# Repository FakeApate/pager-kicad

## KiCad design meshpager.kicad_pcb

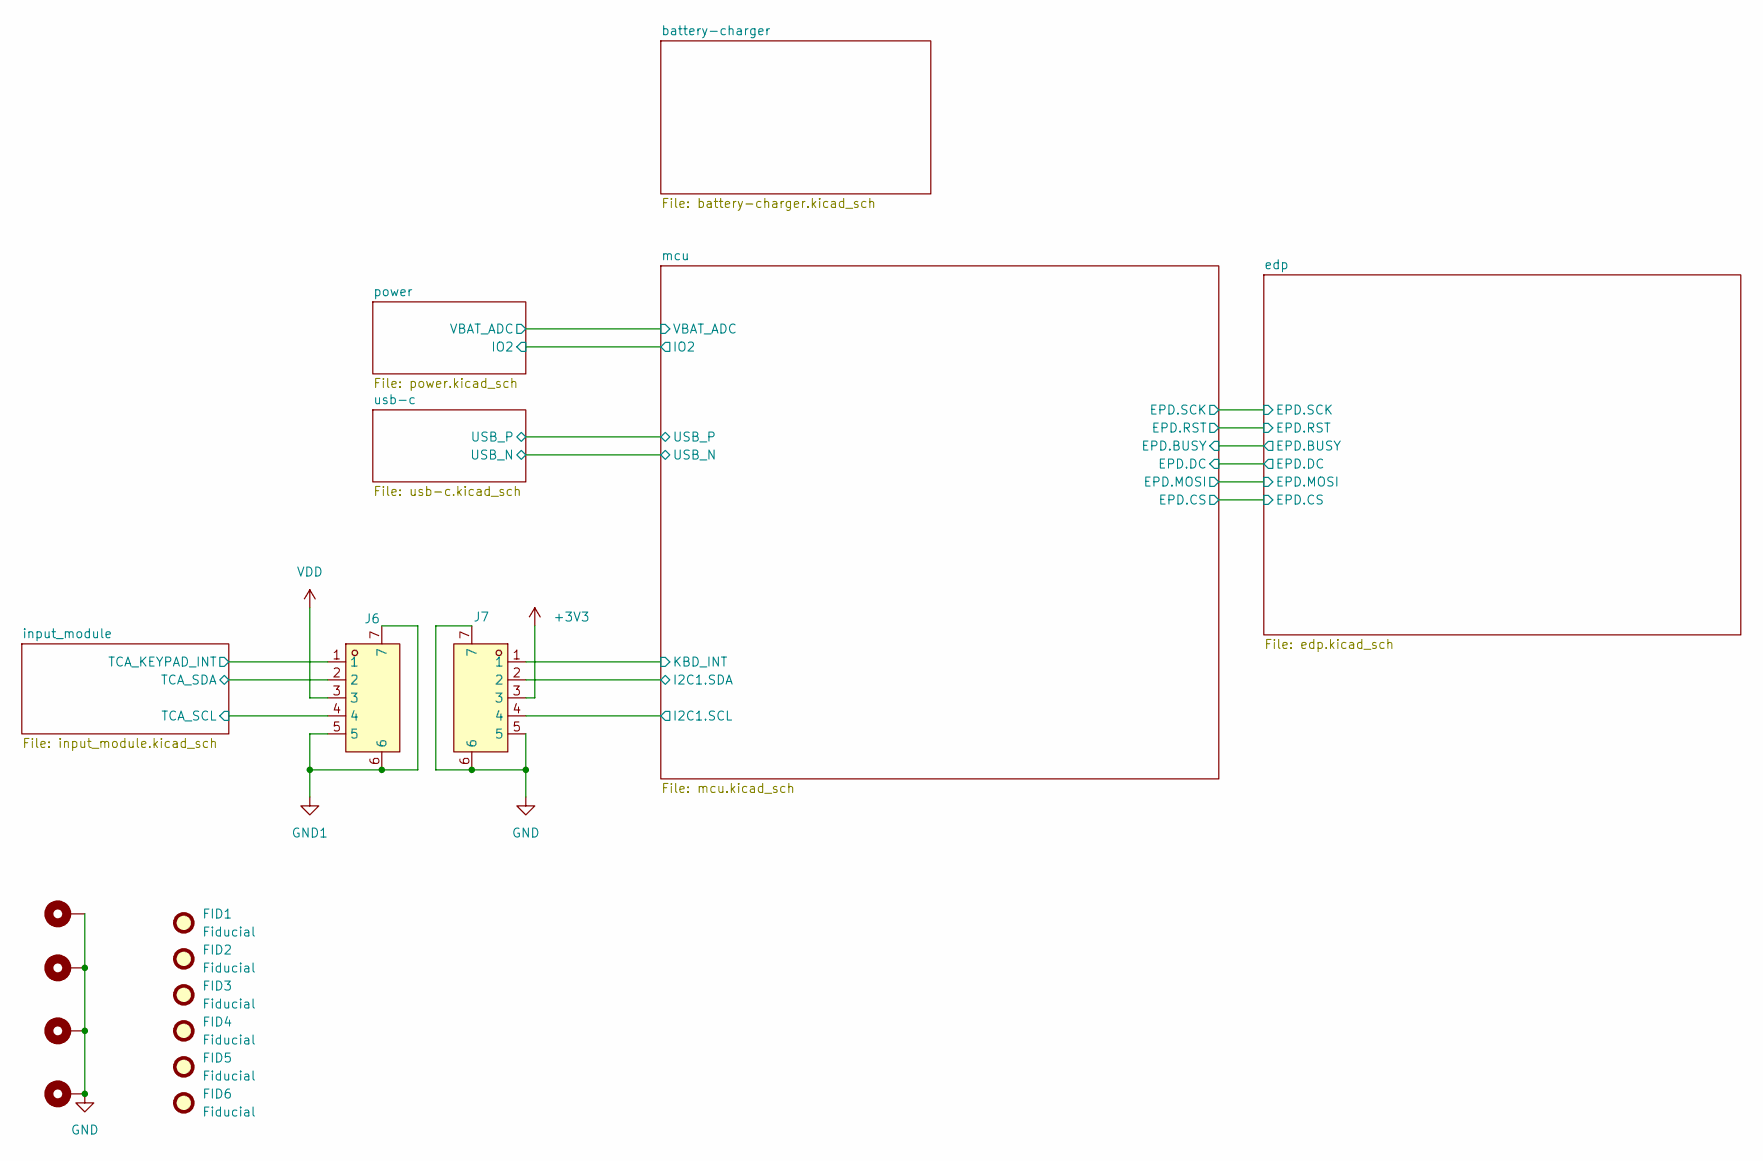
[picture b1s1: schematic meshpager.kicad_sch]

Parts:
FID1, FID2, FID3, FID4, FID5, FID6: Fiducial; Fiducial_1mm_Mask3mm
H5, H6, H7, H8: MountingHole_Pad; MountingHole_2.7mm_M2.5_Pad
J6, J7: HC-FPC-05-09-5RLTAG; CONN-SMD_5P-P0.50_HCTL_HC-FPC-05-09-5RLTAG; MPN HC-FPC-05-09-5RLTAG; LCSC Part C5213747

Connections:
+3V3: J7.3; also elsewhere on the board
/input_module/INT: J6.1; also elsewhere on the board
/input_module/TCA_SCL: J6.4; also elsewhere on the board
/input_module/TCA_SDA: J6.2; also elsewhere on the board
/mcu/I2C1.SCL: J7.4; also elsewhere on the board
/mcu/I2C1.SDA: J7.2; also elsewhere on the board
/mcu/KBD_INT: J7.1; also elsewhere on the board
GND: H5.1 (1_1), H6.1 (1_1), H7.1 (1_1), H8.1 (1_1), J7.5, J7.6, J7.7; also elsewhere on the board
GND1: J6.5, J6.6, J6.7; also elsewhere on the board
VDD: J6.3; also elsewhere on the board

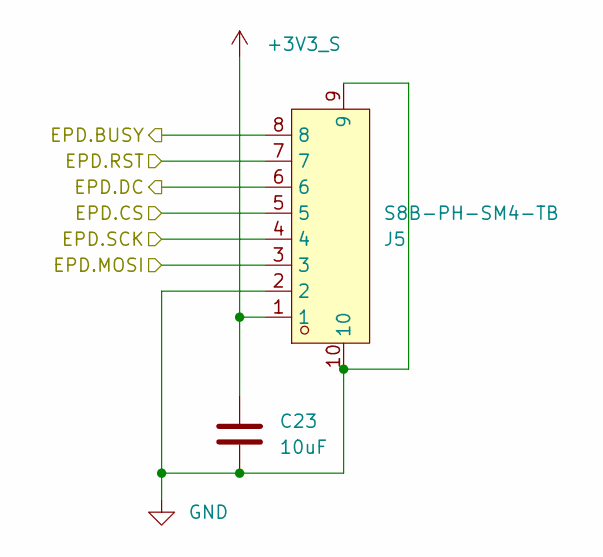
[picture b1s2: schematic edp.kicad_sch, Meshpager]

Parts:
C23: 10uF; C_0603_1608Metric; LCSC C19702
J5: S8B-PH-SM4-TB; CONN-SMD_8P-P2.00_S8B-PH-SM4-TB-LF-SN; MPN S8B-PH-SM4-TB(LF)(SN); LCSC Part C265121

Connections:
+3V3_S: C23.1, J5.1; also elsewhere on the board
/edp/EPD.BUSY: J5.8; also elsewhere on the board
/edp/EPD.CS: J5.5; also elsewhere on the board
/edp/EPD.DC: J5.6; also elsewhere on the board
/edp/EPD.MOSI: J5.3; also elsewhere on the board
/edp/EPD.RST: J5.7; also elsewhere on the board
/edp/EPD.SCK: J5.4; also elsewhere on the board
GND: C23.2, J5.2, J5.9, J5.10; also elsewhere on the board

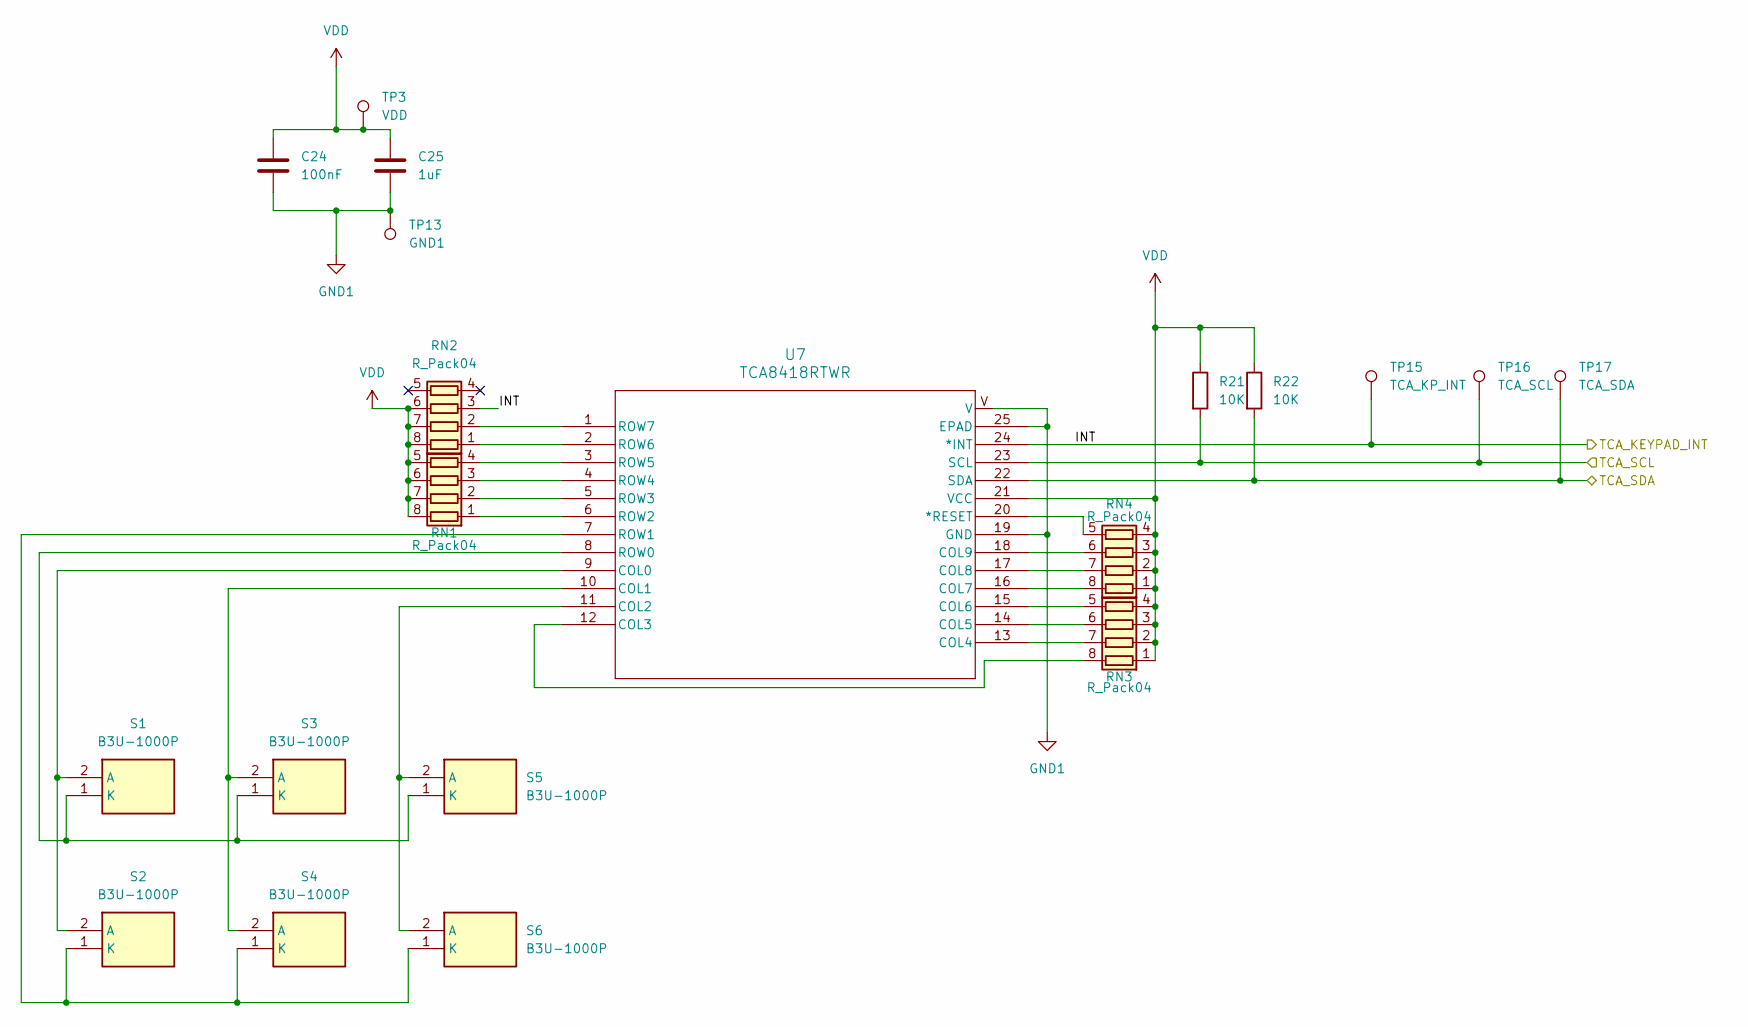
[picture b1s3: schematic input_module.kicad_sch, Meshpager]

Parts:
C24: 100nF; C_0402_1005Metric; LCSC C1525
C25: 1uF; C_0603_1608Metric; LCSC C15849
R21, R22: 10K; R_0402_1005Metric; LCSC C25744
RN1, RN2, RN3, RN4: R_Pack04; R_Array_Convex_4x0603; LCSC C29718
S1, S2, S3, S4, S5, S6: B3U-1000P; Mouser Part Number 653-B3U-1000P
TP3: VDD; TestPoint_Pad_D1.5mm
TP13: GND1; TestPoint_Pad_D1.5mm
TP15: TCA_KP_INT; TestPoint_Pad_D1.5mm
TP16: TCA_SCL; TestPoint_Pad_D1.5mm
TP17: TCA_SDA; TestPoint_Pad_D1.5mm
U7: TCA8418RTWR; WQFN-24-1EP_4x4mm_P0.5mm_EP2.45x2.45mm; LCSC C138713

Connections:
/input_module/INT: RN2.3 (R3.1), TP15.1 (1_1), U7.24 (*INT); also elsewhere on the board
/input_module/TCA_SCL: R21.2, TP16.1 (1_1), U7.23 (SCL); also elsewhere on the board
/input_module/TCA_SDA: R22.2, TP17.1 (1_1), U7.22 (SDA); also elsewhere on the board
GND1: C24.2, C25.2, TP13.1 (1_1), U7.19 (GND), U7.25 (EPAD), U7.V; also elsewhere on the board
unnamed: RN1.1 (R1.1), U7.6 (ROW2)
unnamed: RN1.2 (R2.1), U7.5 (ROW3)
unnamed: RN1.3 (R3.1), U7.4 (ROW4)
unnamed: RN1.4 (R4.1), U7.3 (ROW5)
unnamed: RN2.1 (R1.1), U7.2 (ROW6)
unnamed: RN2.2 (R2.1), U7.1 (ROW7)
unnamed: RN3.8 (R1.2), U7.12 (COL3)
unnamed: RN3.7 (R2.2), U7.13 (COL4)
unnamed: RN3.6 (R3.2), U7.14 (COL5)
unnamed: RN3.5 (R4.2), U7.15 (COL6)
unnamed: RN4.8 (R1.2), U7.16 (COL7)
unnamed: RN4.7 (R2.2), U7.17 (COL8)
unnamed: RN4.6 (R3.2), U7.18 (COL9)
unnamed: RN4.5 (R4.2), U7.20 (*RESET)
unnamed: S1.2 (A), S2.2 (A), U7.9 (COL0)
unnamed: S1.1 (K), S3.1 (K), S5.1 (K), U7.8 (ROW0)
unnamed: S2.1 (K), S4.1 (K), S6.1 (K), U7.7 (ROW1)
unnamed: S3.2 (A), S4.2 (A), U7.10 (COL1)
unnamed: S5.2 (A), S6.2 (A), U7.11 (COL2)
VDD: C24.1, C25.1, R21.1, R22.1, RN1.5 (R4.2), RN1.6 (R3.2), RN1.7 (R2.2), RN1.8 (R1.2), RN2.6 (R3.2), RN2.7 (R2.2), RN2.8 (R1.2), RN3.1 (R1.1), RN3.2 (R2.1), RN3.3 (R3.1), RN3.4 (R4.1), RN4.1 (R1.1), RN4.2 (R2.1), RN4.3 (R3.1), RN4.4 (R4.1), TP3.1 (1_1), U7.21 (VCC); also elsewhere on the board

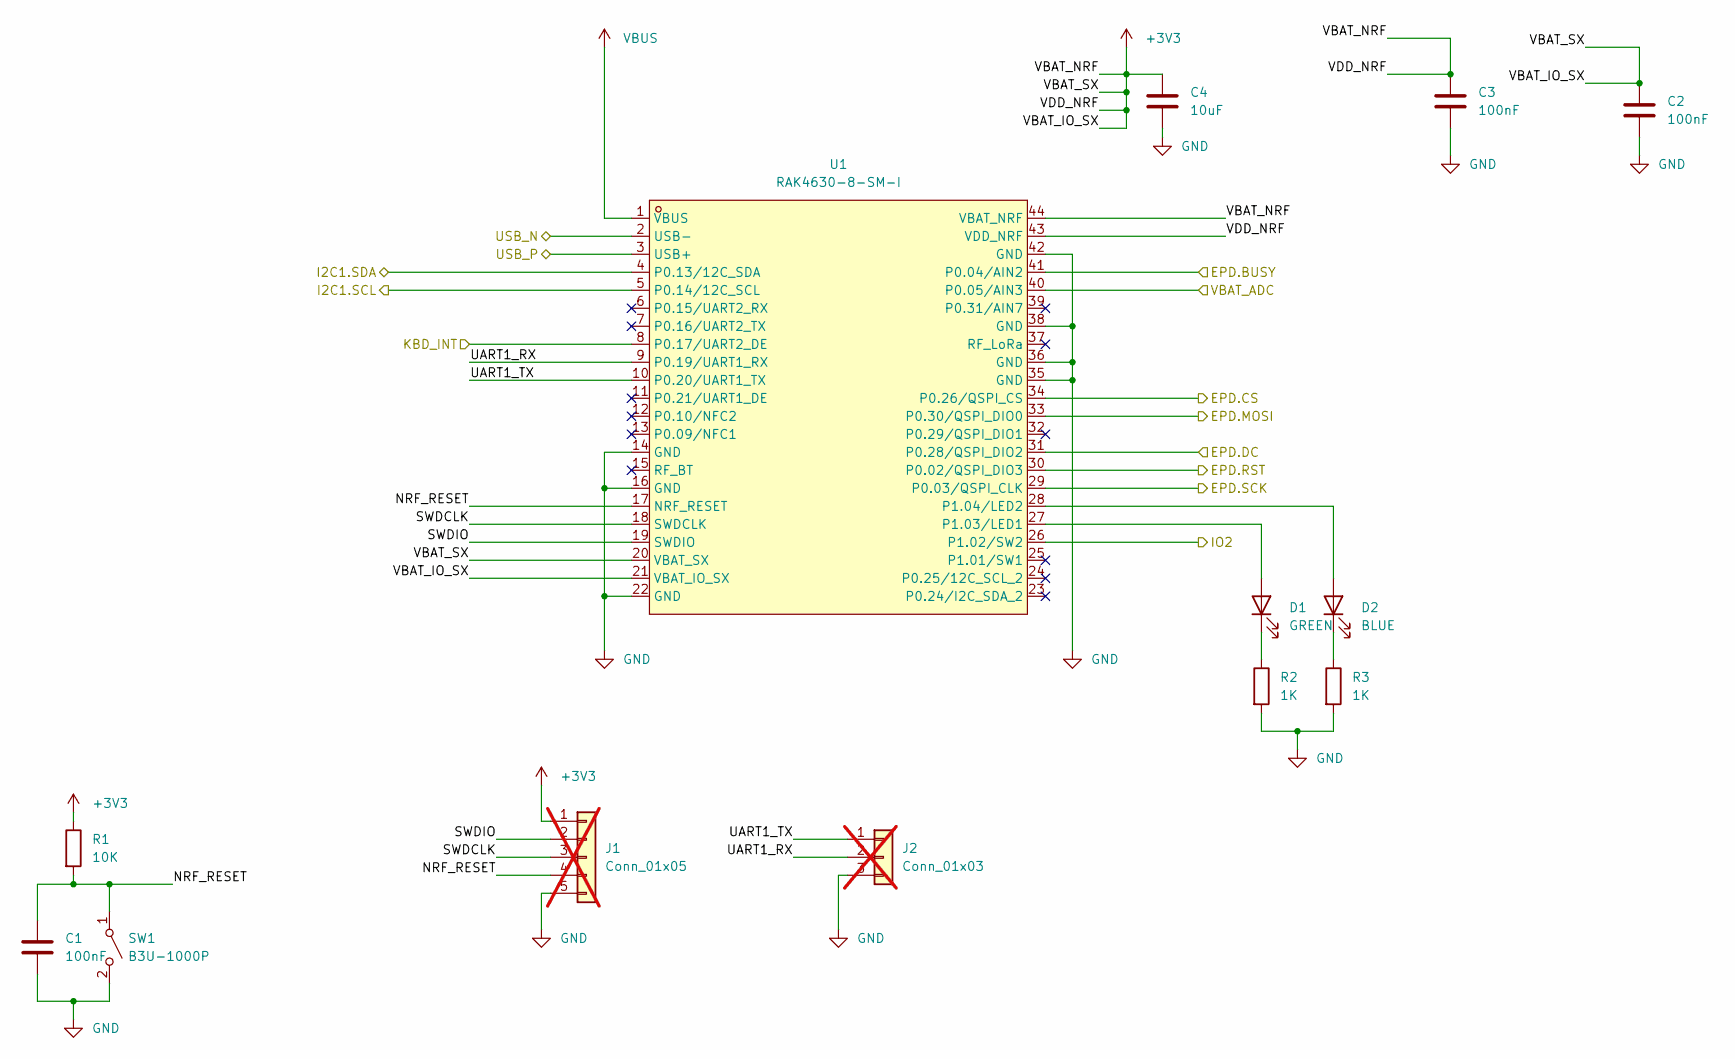
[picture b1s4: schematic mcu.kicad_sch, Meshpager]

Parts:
C1, C2, C3: 100nF; C_0402_1005Metric; LCSC C1525
C4: 10uF; C_0603_1608Metric; LCSC C19702
D1: GREEN; LED_0603_1608Metric; LCSC C12624
D2: BLUE; LED_0603_1608Metric; LCSC C2288
J1: Conn_01x05; PinHeader_1x05_P1.27mm_Vertical; not fitted
J2: Conn_01x03; PinHeader_1x03_P1.27mm_Vertical; not fitted
R1: 10K; R_0402_1005Metric; LCSC C25744
R2, R3: 1K; R_0402_1005Metric; LCSC C11702
SW1: B3U-1000P; LCSC C231329
U1: RAK4630-8-SM-I; COMM-SMD_44P-L23.0-W15.0-P1.20_RAK4630-8-SM-I; MPN RAk4630-8-SM-I; LCSC Part C32315253

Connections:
+3V3: C2.1, C3.1, C4.1, J1.1, R1.1, U1.20 (VBAT_SX), U1.21 (VBAT_IO_SX), U1.43 (VDD_NRF), U1.44 (VBAT_NRF); also elsewhere on the board
/edp/EPD.BUSY: U1.41 (P0.04/AIN2); also elsewhere on the board
/edp/EPD.CS: U1.34 (P0.26/QSPI_CS); also elsewhere on the board
/edp/EPD.DC: U1.31 (P0.28/QSPI_DIO2); also elsewhere on the board
/edp/EPD.MOSI: U1.33 (P0.30/QSPI_DIO0); also elsewhere on the board
/edp/EPD.RST: U1.30 (P0.02/QSPI_DIO3); also elsewhere on the board
/edp/EPD.SCK: U1.29 (P0.03/QSPI_CLK); also elsewhere on the board
/mcu/I2C1.SCL: U1.5 (P0.14/12C_SCL); also elsewhere on the board
/mcu/I2C1.SDA: U1.4 (P0.13/12C_SDA); also elsewhere on the board
/mcu/IO2: U1.26 (P1.02/SW2); also elsewhere on the board
/mcu/KBD_INT: U1.8 (P0.17/UART2_DE); also elsewhere on the board
/mcu/NRF_RESET: C1.1, J1.4, R1.2, SW1.1 (A), U1.17 (NRF_RESET)
/mcu/SWDCLK: J1.3, U1.18 (SWDCLK)
/mcu/SWDIO: J1.2, U1.19 (SWDIO)
/mcu/UART1_RX: J2.2, U1.9 (P0.19/UART1_RX)
/mcu/UART1_TX: J2.1, U1.10 (P0.20/UART1_TX)
/mcu/USB_N: U1.2 (USB-); also elsewhere on the board
/mcu/USB_P: U1.3 (USB+); also elsewhere on the board
/mcu/VBAT_ADC: U1.40 (P0.05/AIN3); also elsewhere on the board
GND: C1.2, C2.2, C3.2, C4.2, J1.5, J2.3, R2.2, R3.2, SW1.2 (B), U1.14 (GND), U1.16 (GND), U1.22 (GND), U1.35 (GND), U1.36 (GND), U1.38 (GND), U1.42 (GND); also elsewhere on the board
unnamed: D1.2 (A), U1.27 (P1.03/LED1)
unnamed: D1.1 (K), R2.1
unnamed: D2.2 (A), U1.28 (P1.04/LED2)
unnamed: D2.1 (K), R3.1
VBUS: U1.1 (VBUS); also elsewhere on the board

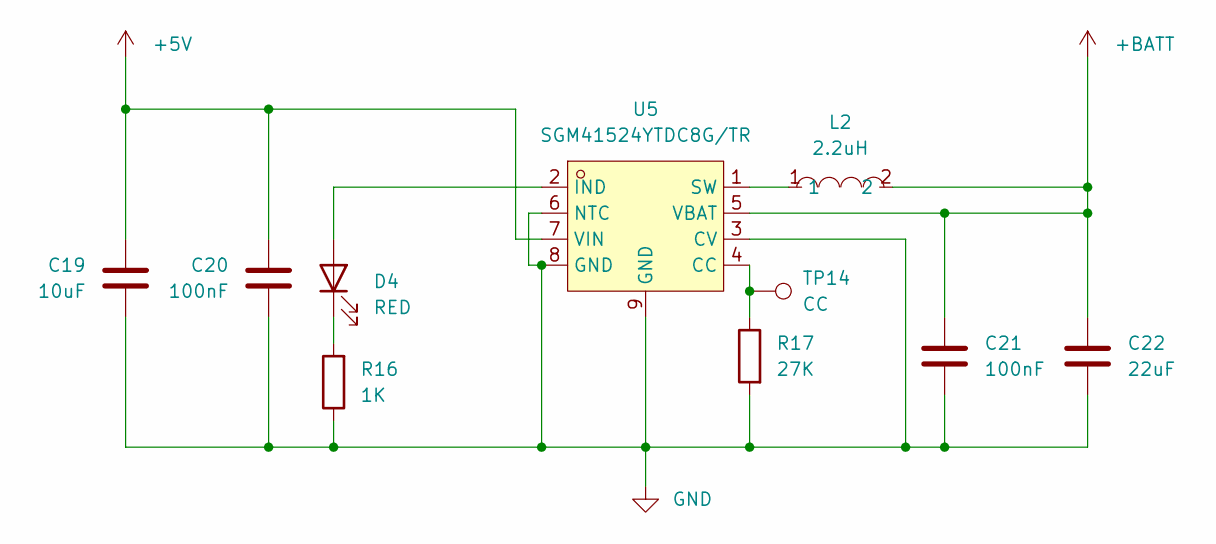
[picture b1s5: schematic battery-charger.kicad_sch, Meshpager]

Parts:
C19: 10uF; C_0603_1608Metric; LCSC C19702
C20, C21: 100nF; C_0402_1005Metric; LCSC C1525
C22: 22uF; C_0805_2012Metric; LCSC C45783
D4: RED; LED_0603_1608Metric; LCSC C2286
L2: 2.2uH; IND-SMD_L3.0-W3.0_SWPA3010S; MPN SWPA3012S2R2MT; LCSC Part C36402
R16: 1K; R_0402_1005Metric; LCSC C11702
R17: 27K; R_0402_1005Metric; LCSC C2933084
TP14: CC; TestPoint_Pad_D1.5mm
U5: SGM41524YTDC8G/TR; DFN-8_L3.0-W2.0-P0.50-TL-EP-1; MPN SGM41524YTDC8G/TR; LCSC Part C699852

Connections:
+5V: C19.2, C20.1, U5.7 (VIN); also elsewhere on the board
+BATT: C21.1, C22.2, L2.2, U5.5 (VBAT); also elsewhere on the board
GND: C19.1, C20.2, C21.2, C22.1, R16.1, R17.2, U5.3 (CV), U5.6 (NTC), U5.8 (GND), U5.9 (GND); also elsewhere on the board
unnamed: D4.2 (A), U5.2 (IND)
unnamed: D4.1 (K), R16.2
unnamed: R17.1, TP14.1 (1_1), U5.4 (CC)
unnamed: L2.1, U5.1 (SW)

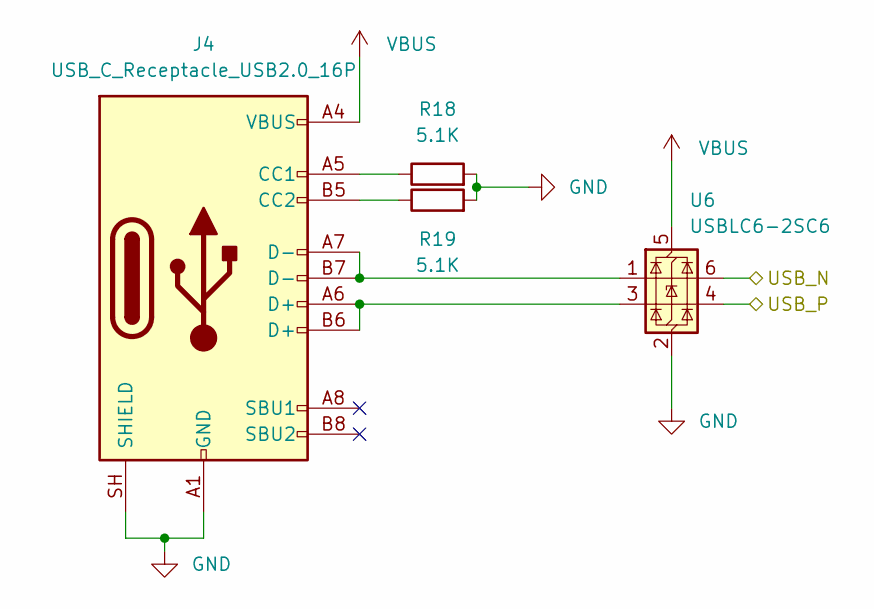
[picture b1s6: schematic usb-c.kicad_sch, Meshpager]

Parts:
J4: USB_C_Receptacle_USB2.0_16P; USB_C_Receptacle_G-Switch_GT-USB-7010ASV; LCSC Part C2988369
R18, R19: 5.1K; R_0402_1005Metric; LCSC C25905
U6: USBLC6-2SC6; SOT-23-6; LCSC C7519

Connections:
/mcu/USB_N: U6.6 (I/O1); also elsewhere on the board
/mcu/USB_P: U6.4 (I/O2); also elsewhere on the board
GND: J4.A1 (GND), J4.A12 (GND), J4.B1 (GND), J4.B12 (GND), J4.SH (SHIELD), R18.2, R19.2, U6.2 (GND); also elsewhere on the board
unnamed: J4.A5 (CC1), R18.1
unnamed: J4.B5 (CC2), R19.1
unnamed: J4.A6 (D+), J4.B6 (D+), U6.3 (I/O2)
unnamed: J4.A7 (D-), J4.B7 (D-), U6.1 (I/O1)
VBUS: J4.A4 (VBUS), J4.A9 (VBUS), J4.B4 (VBUS), J4.B9 (VBUS), U6.5 (VBUS); also elsewhere on the board

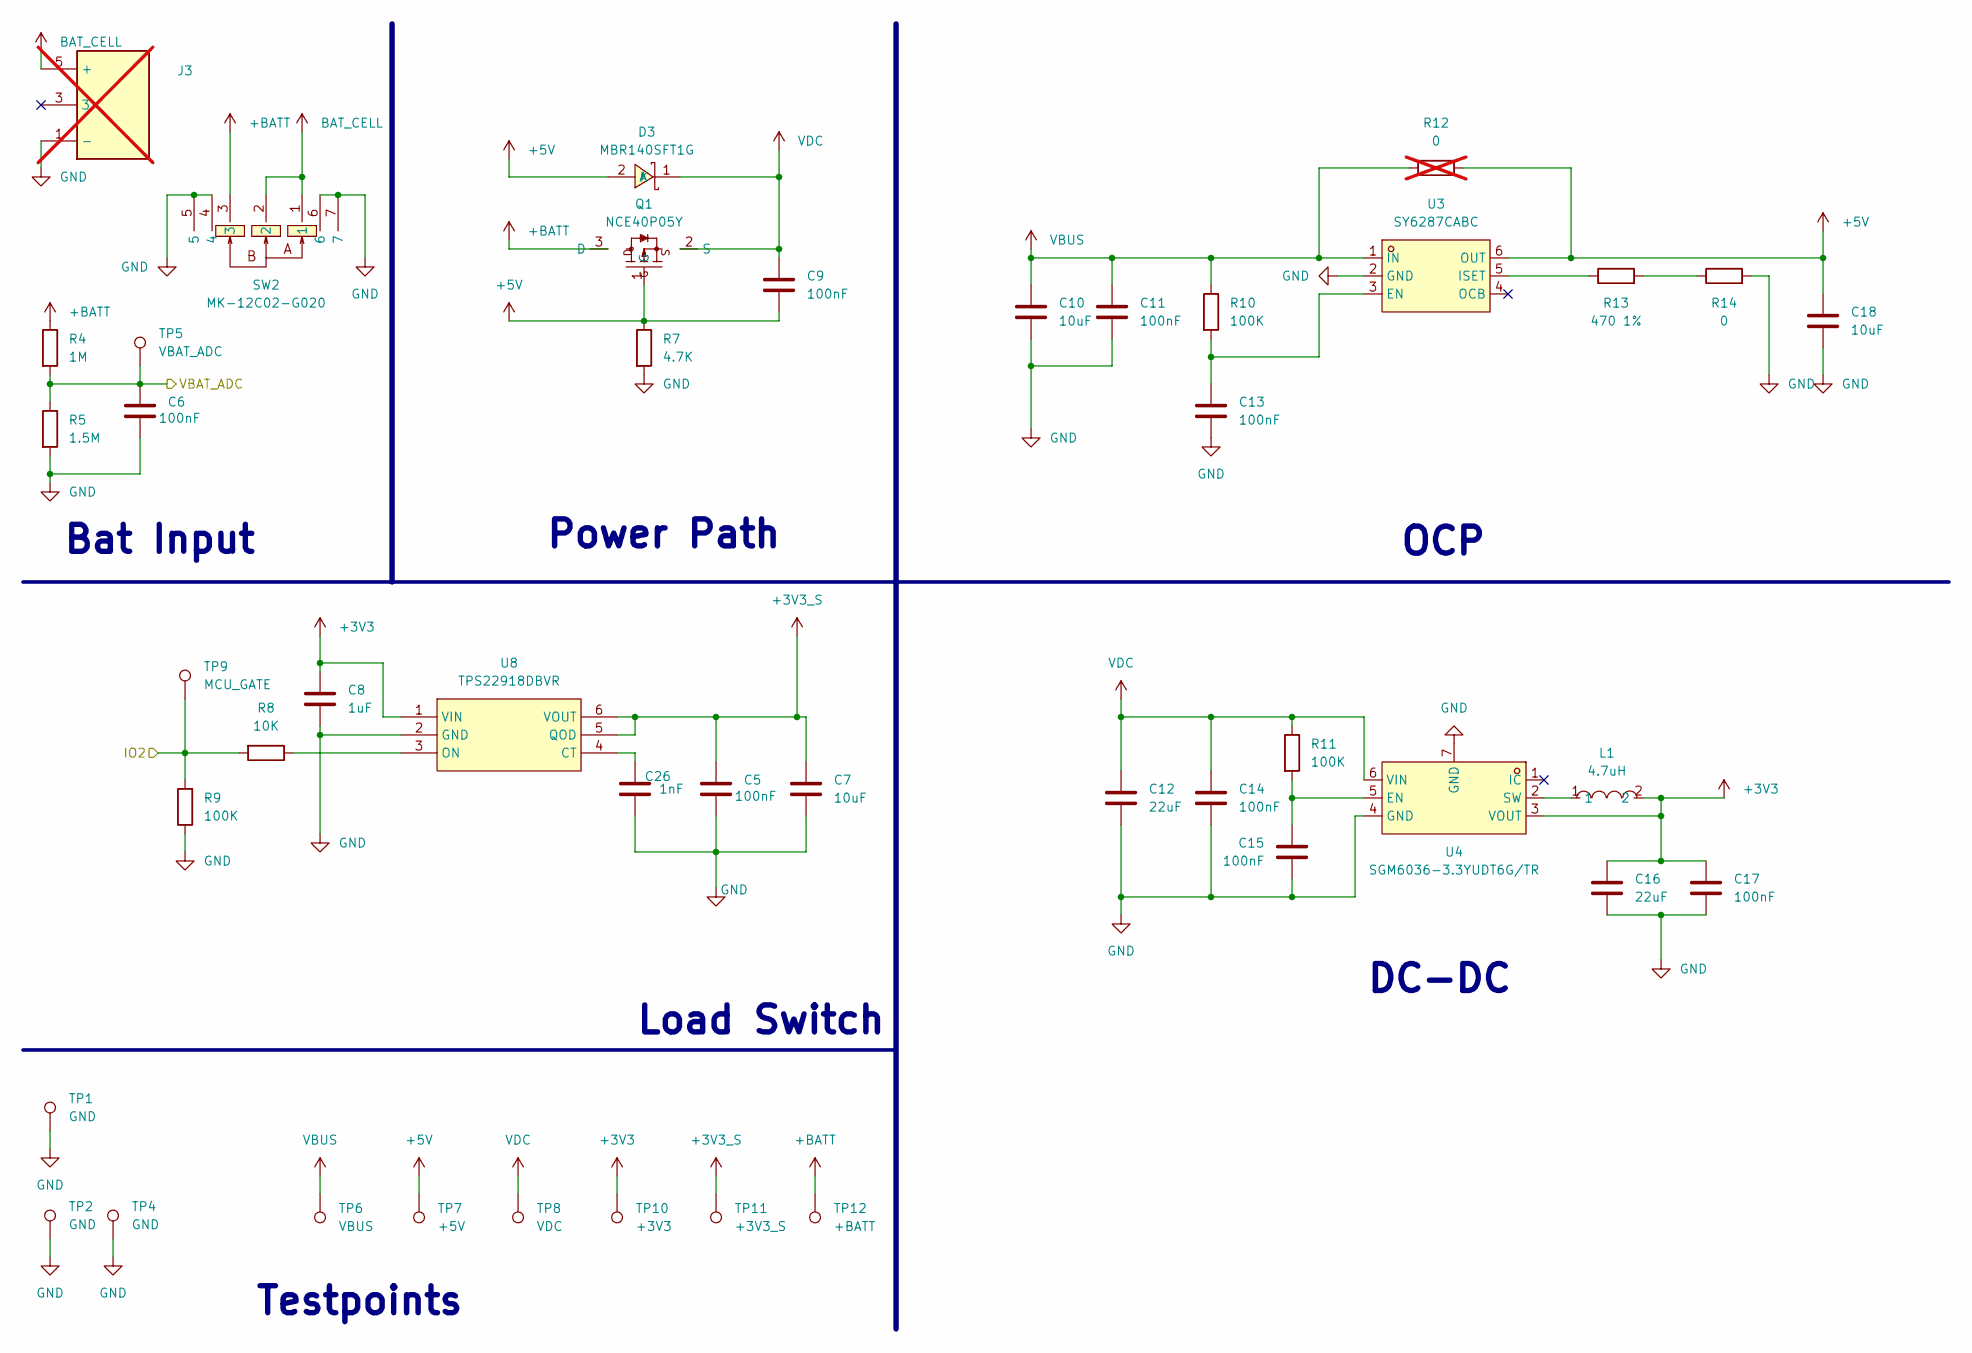
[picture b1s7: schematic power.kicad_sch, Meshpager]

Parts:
C5, C6, C9, C11, C13, C14, C15, C17: 100nF; C_0402_1005Metric; LCSC C1525
C7, C10, C18: 10uF; C_0603_1608Metric; LCSC C19702
C8: 1uF; C_0603_1608Metric; LCSC C15849
C12, C16: 22uF; C_0805_2012Metric; LCSC C45783
C26: 1nF; C_0402_1005Metric
D3: MBR140SFT1G; SOD-123F_L2.8-W1.8-LS3.7-RD; MPN MBR140SFT1G; LCSC Part C43381
J3: 009155003301006; Mouser Part Number 581-009155003301006; not fitted
L1: 4.7uH; IND-SMD_L3.0-W3.0_FNR30XXS; MPN SWPA3012S4R7MT; LCSC Part C83415
Q1: NCE40P05Y; SOT-23-3_L2.9-W1.6-P1.90-LS2.8-BR; MPN NCE40P05Y; LCSC Part C163738
R4: 1M; R_0402_1005Metric; LCSC C26083
R5: 1.5M; R_0402_1005Metric; LCSC C22276
R7: 4.7K; R_0402_1005Metric; LCSC C25900
R8: 10K; R_0402_1005Metric; LCSC C25744
R9, R10, R11: 100K; R_0402_1005Metric; LCSC C25741
R12: 0; R_0805_2012Metric_Pad1.20x1.40mm_HandSolder; LCSC C17477; not fitted
R13: 470 1%; R_0402_1005Metric; LCSC C25117
R14: 0; R_0805_2012Metric_Pad1.20x1.40mm_HandSolder; LCSC C17477
SW2: MK-12C02-G020; SW-SMD_MK-12C02-G020; MPN MK-12C02-G020; LCSC Part C963206
TP1, TP2, TP4: GND; TestPoint_Pad_D1.5mm
TP5: VBAT_ADC; TestPoint_Pad_D1.5mm
TP6: VBUS; TestPoint_Pad_D1.5mm
TP7: +5V; TestPoint_Pad_D1.5mm
TP8: VDC; TestPoint_Pad_D1.5mm
TP9: MCU_GATE; TestPoint_Pad_D1.5mm
TP10: +3V3; TestPoint_Pad_D1.5mm
TP11: +3V3_S; TestPoint_Pad_D1.5mm
TP12: +BATT; TestPoint_Pad_D1.5mm
U3: SY6287CABC; SOT-23-6_L2.9-W1.6-P0.95-LS2.9-BL; MPN SY6287CABC; LCSC Part C3013652
U4: SGM6036-3.3YUDT6G/TR; UTDFN-6_L2.0-W1.5-P0.50-BL-EP; MPN SGM6036-3.3YUDT6G/TR; LCSC Part C5153601
U8: TPS22918DBVR; SOT-23-6_L2.9-W1.6-P0.95-LS2.8-BR; MPN TPS22918DBVR; LCSC Part C131941

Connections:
+3V3: C8.1, C16.2, C17.2, L1.2, TP10.1 (1_1), U4.3 (VOUT), U8.1 (VIN); also elsewhere on the board
+3V3_S: C5.1, C7.1, TP11.1 (1_1), U8.5 (QOD), U8.6 (VOUT); also elsewhere on the board
+5V: C9.2, C18.1, D3.2 (A), Q1.1 (G), R7.1, R12.2, TP7.1 (1_1), U3.6 (OUT); also elsewhere on the board
+BATT: Q1.3 (D), R4.1, SW2.3, TP12.1 (1_1); also elsewhere on the board
/mcu/IO2: R8.2, R9.2, TP9.1 (1_1); also elsewhere on the board
/mcu/VBAT_ADC: C6.1, R4.2, R5.1, TP5.1 (1_1); also elsewhere on the board
BAT_CELL: J3.5 (+), SW2.1, SW2.2
GND: C5.2, C6.2, C7.2, C8.2, C10.2, C11.2, C12.2, C13.2, C14.2, C15.2, C16.1, C17.1, C18.2, C26.2, J3.1 (-), R5.2, R7.2, R9.1, R14.2, SW2.4, SW2.5, SW2.6, SW2.7, TP1.1 (1_1), TP2.1 (1_1), TP4.1 (1_1), U3.2 (GND), U4.4 (GND), U4.7 (GND), U8.2 (GND); also elsewhere on the board
unnamed: R13.2, R14.1
unnamed: C13.1, R10.2, U3.3 (EN)
unnamed: R13.1, U3.5 (ISET)
unnamed: C15.1, R11.2, U4.5 (EN)
unnamed: L1.1, U4.2 (SW)
unnamed: C26.1, U8.4 (CT)
unnamed: R8.1, U8.3 (ON)
VBUS: C10.1, C11.1, R10.1, R12.1, TP6.1 (1_1), U3.1 (IN); also elsewhere on the board
VDC: C9.1, C12.1, C14.1, D3.1 (K), Q1.2 (S), R11.1, TP8.1 (1_1), U4.6 (VIN)

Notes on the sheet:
Load Switch
OCP
Power Path
DC-DC
Bat Input
Testpoints

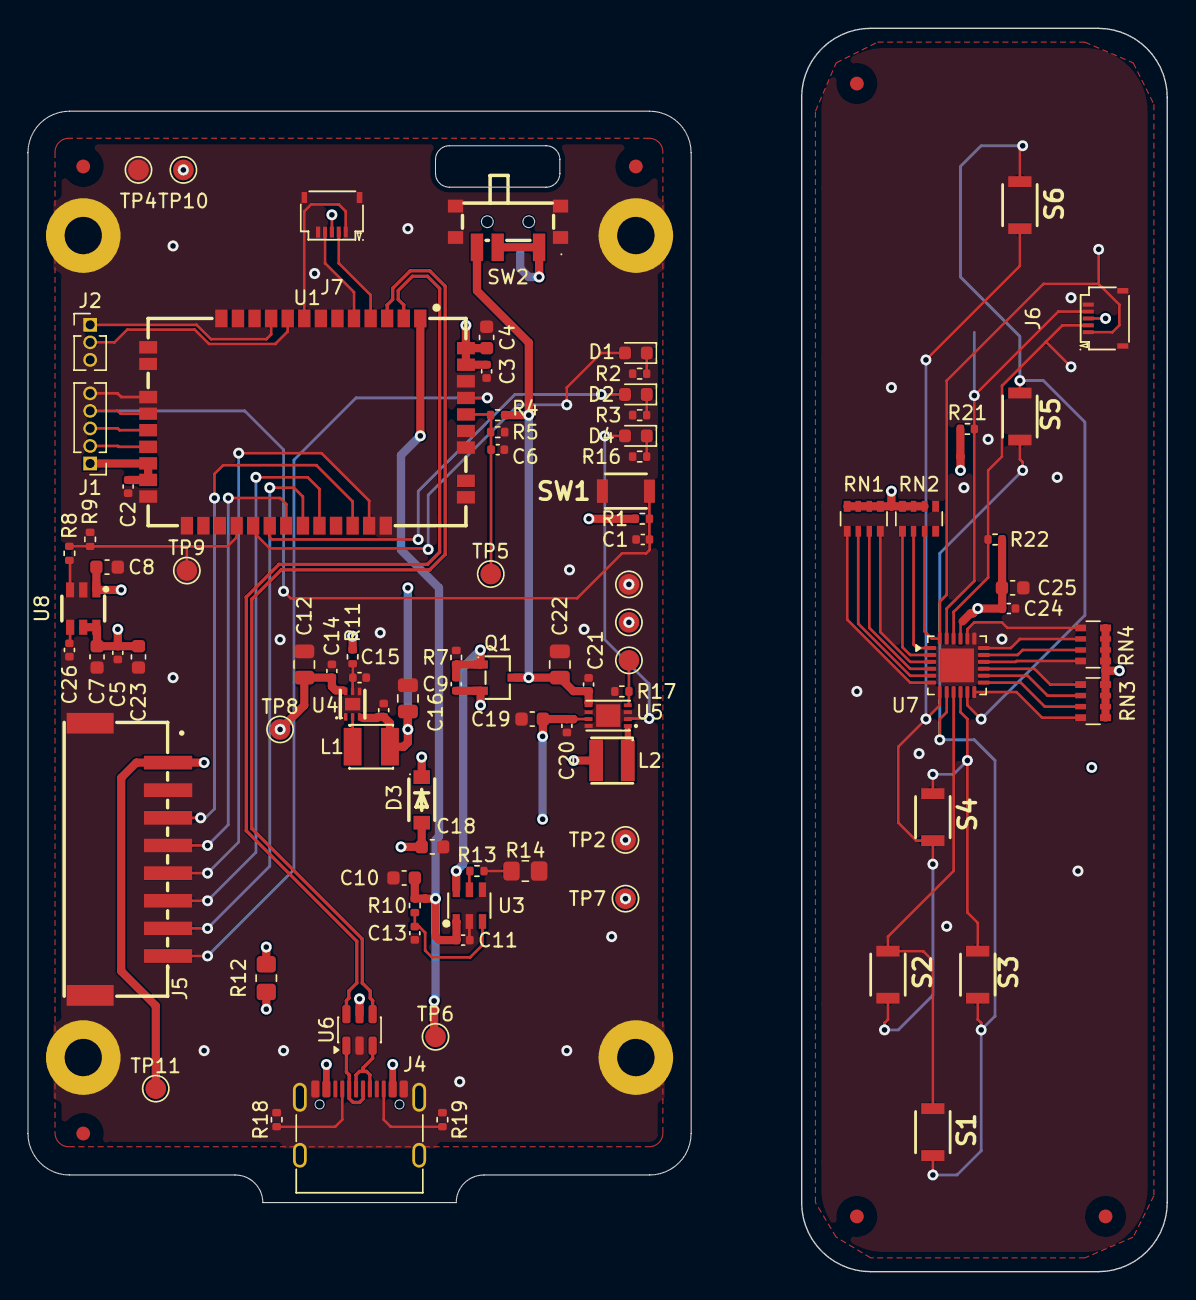
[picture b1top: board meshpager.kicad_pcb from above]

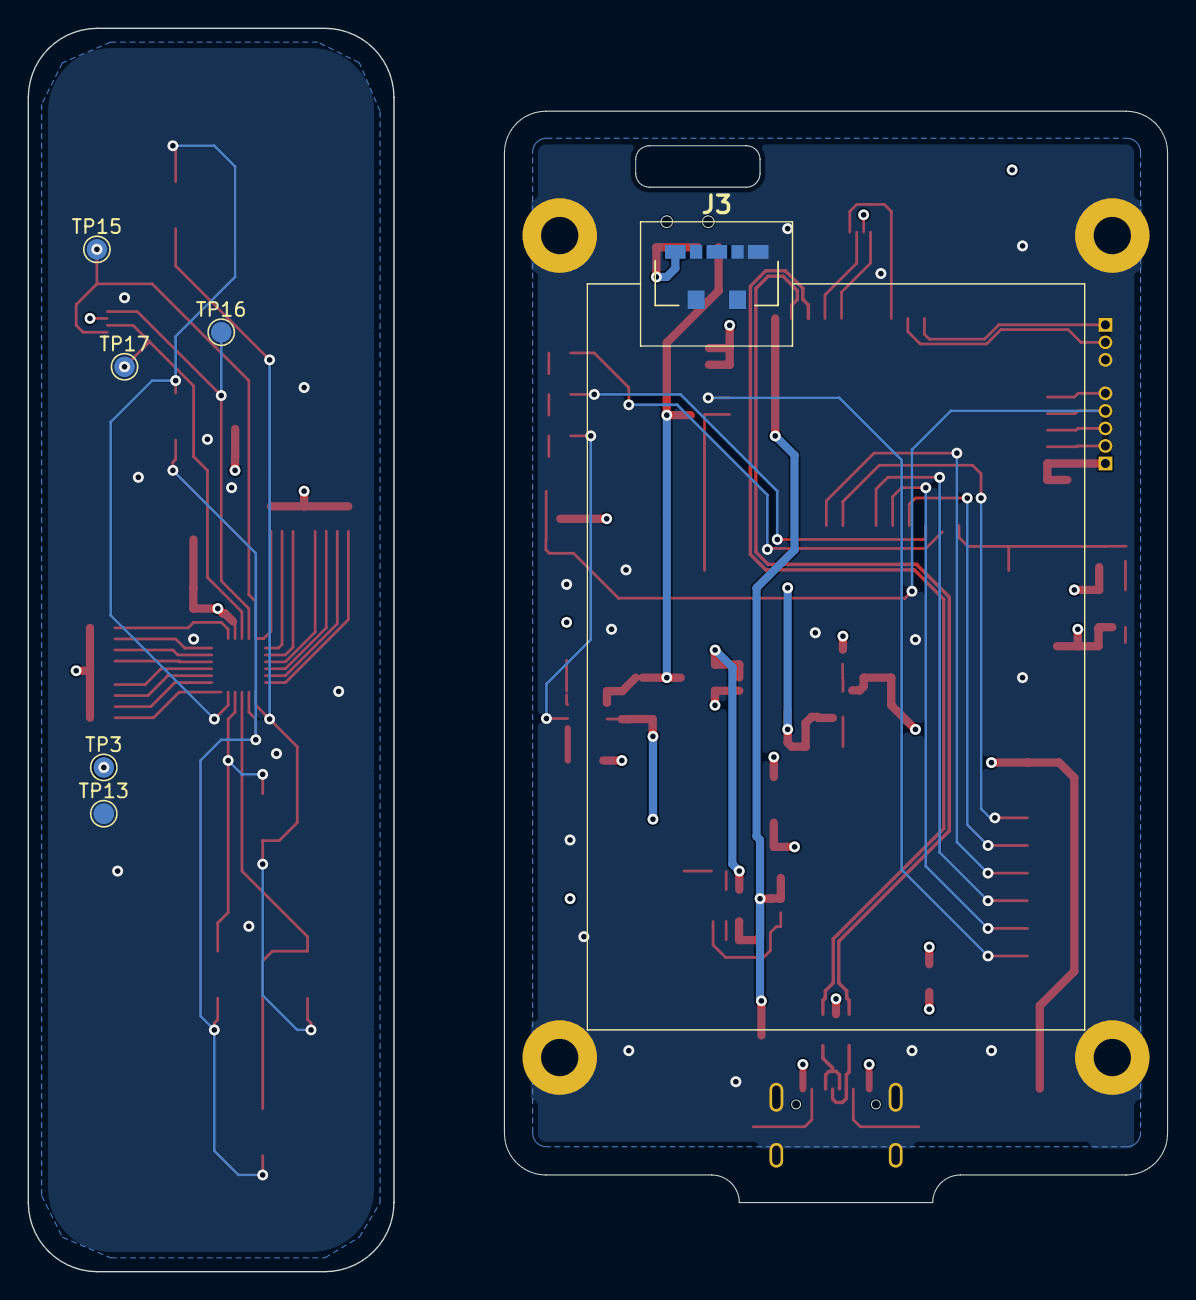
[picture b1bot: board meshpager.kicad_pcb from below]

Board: 4 copper layers, 82.5 x 90.0 mm, 107 parts (6 on the bottom side), 69 nets.

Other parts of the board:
Input: Board
Main: Board
